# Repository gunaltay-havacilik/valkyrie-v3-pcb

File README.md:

# Valkyrie Flight Control Computer V3.1

Made using primarily KiCad version 9.0<br/>
Some 3D files might not be assigned correctly. You have been warned.<br/>
Uses JLCPCB JLC04161H-7628 stackup, 4 layer.

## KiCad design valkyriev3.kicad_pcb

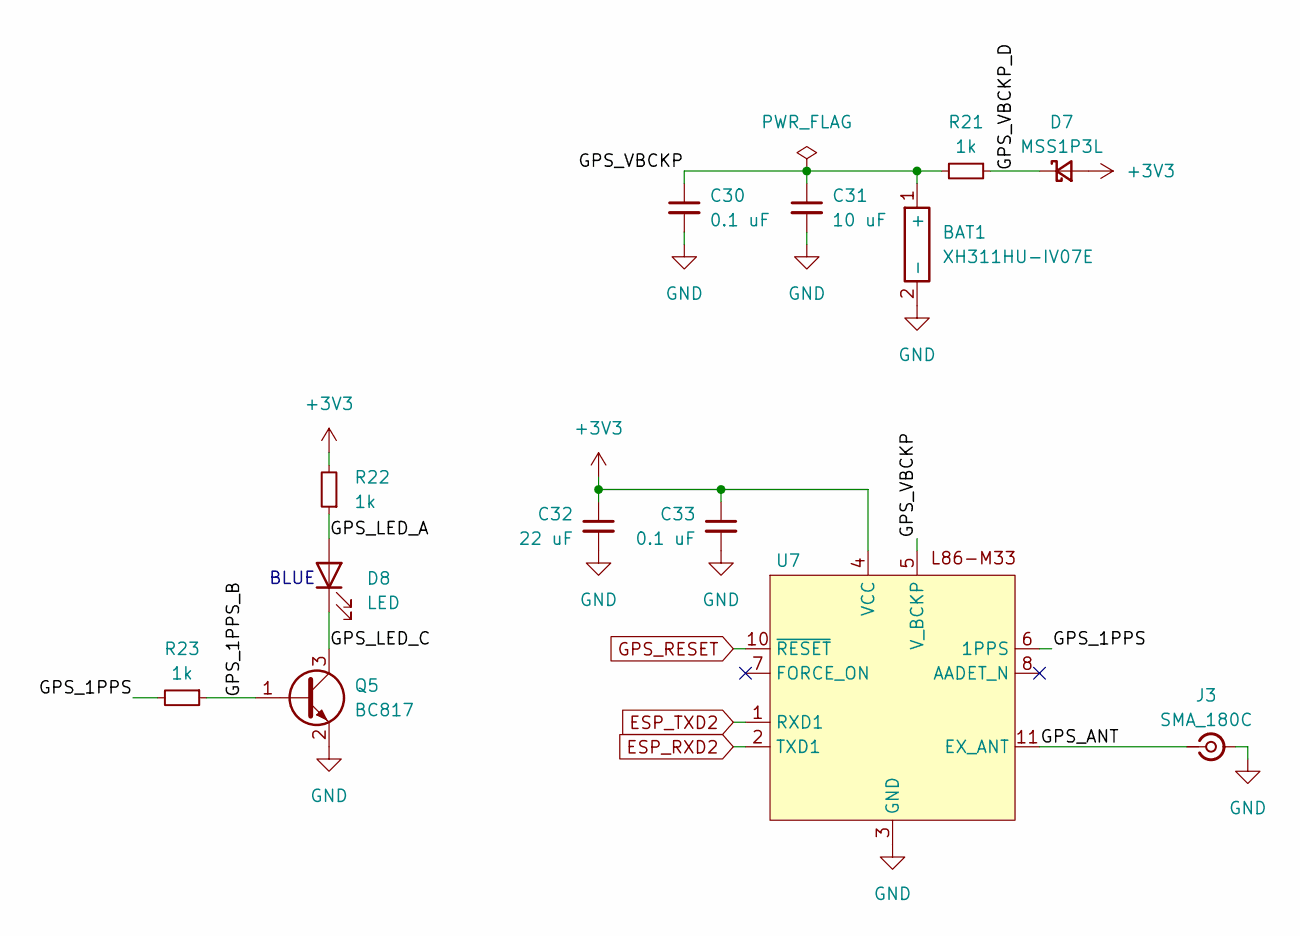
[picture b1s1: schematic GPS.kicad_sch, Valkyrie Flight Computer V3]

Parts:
BAT1: XH311HU-IV07E
C30, C33: 0.1 uF; C_0603_1608Metric
C31: 10 uF; C_0603_1608Metric
C32: 22 uF; C_0603_1608Metric
D7: MSS1P3L; D_MicroSMP_AK
D8: LED; LED_0603_1608Metric
J3: SMA_180C; SMA_Amphenol_132134-16_Vertical
Q5: BC817; SOT-23
R21, R22, R23: 1k; R_0603_1608Metric
U7: Quectel_L86-M33

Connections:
+3V3: C32.1, C33.1, D7.2 (A), R22.2, U7.4 (VCC); also elsewhere on the board
/GPS/GPS_1PPS: R23.2, U7.6 (1PPS)
/GPS/GPS_1PPS_B: Q5.1 (B), R23.1
/GPS/GPS_ANT: J3.1 (In), U7.11 (EX_ANT)
/GPS/GPS_LED_A: D8.2 (A), R22.1
/GPS/GPS_LED_C: D8.1 (K), Q5.3 (C)
/GPS/GPS_VBCKP: BAT1.1 (+), C30.1, C31.1, R21.2, U7.5 (V_BCKP)
/GPS/GPS_VBCKP_D: D7.1 (K), R21.1
ESP_RXD2: U7.2 (TXD1); also elsewhere on the board
ESP_TXD2: U7.1 (RXD1); also elsewhere on the board
GND: BAT1.2 (-), C30.2, C31.2, C32.2, C33.2, J3.2 (Ext), Q5.2 (E), U7.3 (GND), U7.12 (GND); also elsewhere on the board
GPS_RESET: U7.10 (~RESET); also elsewhere on the board

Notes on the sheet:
BLUE

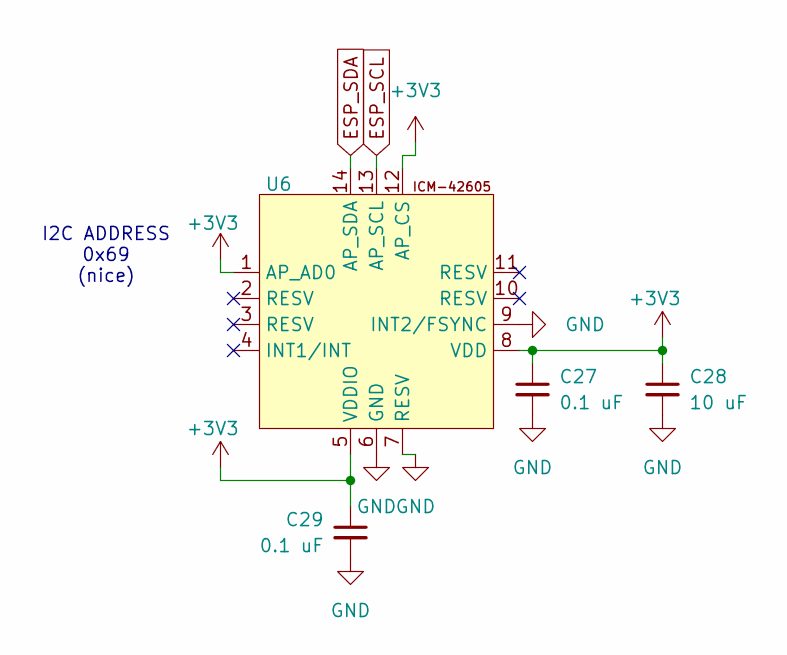
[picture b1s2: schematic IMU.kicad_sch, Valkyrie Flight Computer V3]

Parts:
C27, C29: 0.1 uF; C_0603_1608Metric
C28: 10 uF; C_0603_1608Metric
U6: LGA-14_3x2.5mm_P0.5mm_LayoutBorder3x4y

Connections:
+3V3: C27.1, C28.1, C29.1, U6.1 (AP_AD0), U6.5 (VDDIO), U6.8 (VDD), U6.12 (AP_CS); also elsewhere on the board
ESP_SCL: U6.13 (AP_SCL); also elsewhere on the board
ESP_SDA: U6.14 (AP_SDA); also elsewhere on the board
GND: C27.2, C28.2, C29.2, U6.6 (GND), U6.7 (RESV), U6.9 (INT2/FSYNC); also elsewhere on the board

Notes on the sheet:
I2C ADDRESS 0x69 (nice)

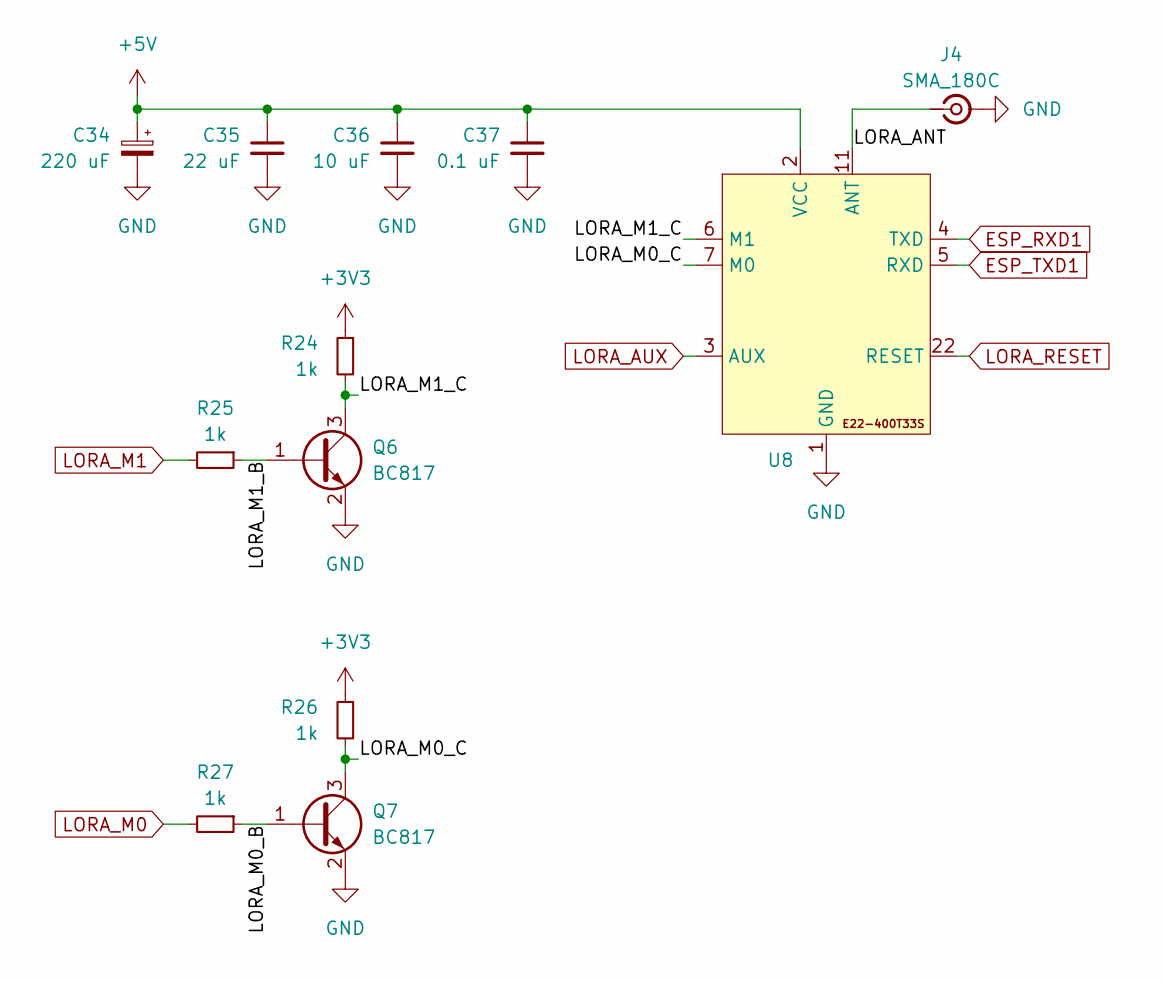
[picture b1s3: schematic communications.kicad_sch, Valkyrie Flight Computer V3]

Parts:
C34: 220 uF; CP_Elec_6.3x7.7
C35: 22 uF; C_0603_1608Metric
C36: 10 uF; C_0603_1608Metric
C37: 0.1 uF; C_0603_1608Metric
J4: SMA_180C; SMA_Amphenol_132134-16_Vertical
Q6, Q7: BC817; SOT-23
R24, R25, R26, R27: 1k; R_0603_1608Metric
U8: E22-400T33S

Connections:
+3V3: R24.1, R26.1; also elsewhere on the board
+5V: C34.1, C35.1, C36.1, C37.1, U8.2 (VCC); also elsewhere on the board
/Communications/LORA_ANT: J4.1 (In), U8.11 (ANT)
/Communications/LORA_M0_B: Q7.1 (B), R27.1
/Communications/LORA_M0_C: Q7.3 (C), R26.2, U8.7 (M0)
/Communications/LORA_M1_B: Q6.1 (B), R25.1
/Communications/LORA_M1_C: Q6.3 (C), R24.2, U8.6 (M1)
ESP_RXD1: U8.4 (TXD); also elsewhere on the board
ESP_TXD1: U8.5 (RXD); also elsewhere on the board
GND: C34.2, C35.2, C36.2, C37.2, J4.2 (Ext), Q6.2 (E), Q7.2 (E), U8.1 (GND), U8.12 (GND), U8.13 (GND), U8.14 (GND), U8.23 (GND); also elsewhere on the board
LORA_AUX: U8.3 (AUX); also elsewhere on the board
LORA_M0: R27.2; also elsewhere on the board
LORA_M1: R25.2; also elsewhere on the board
LORA_RESET: U8.22 (RESET); also elsewhere on the board

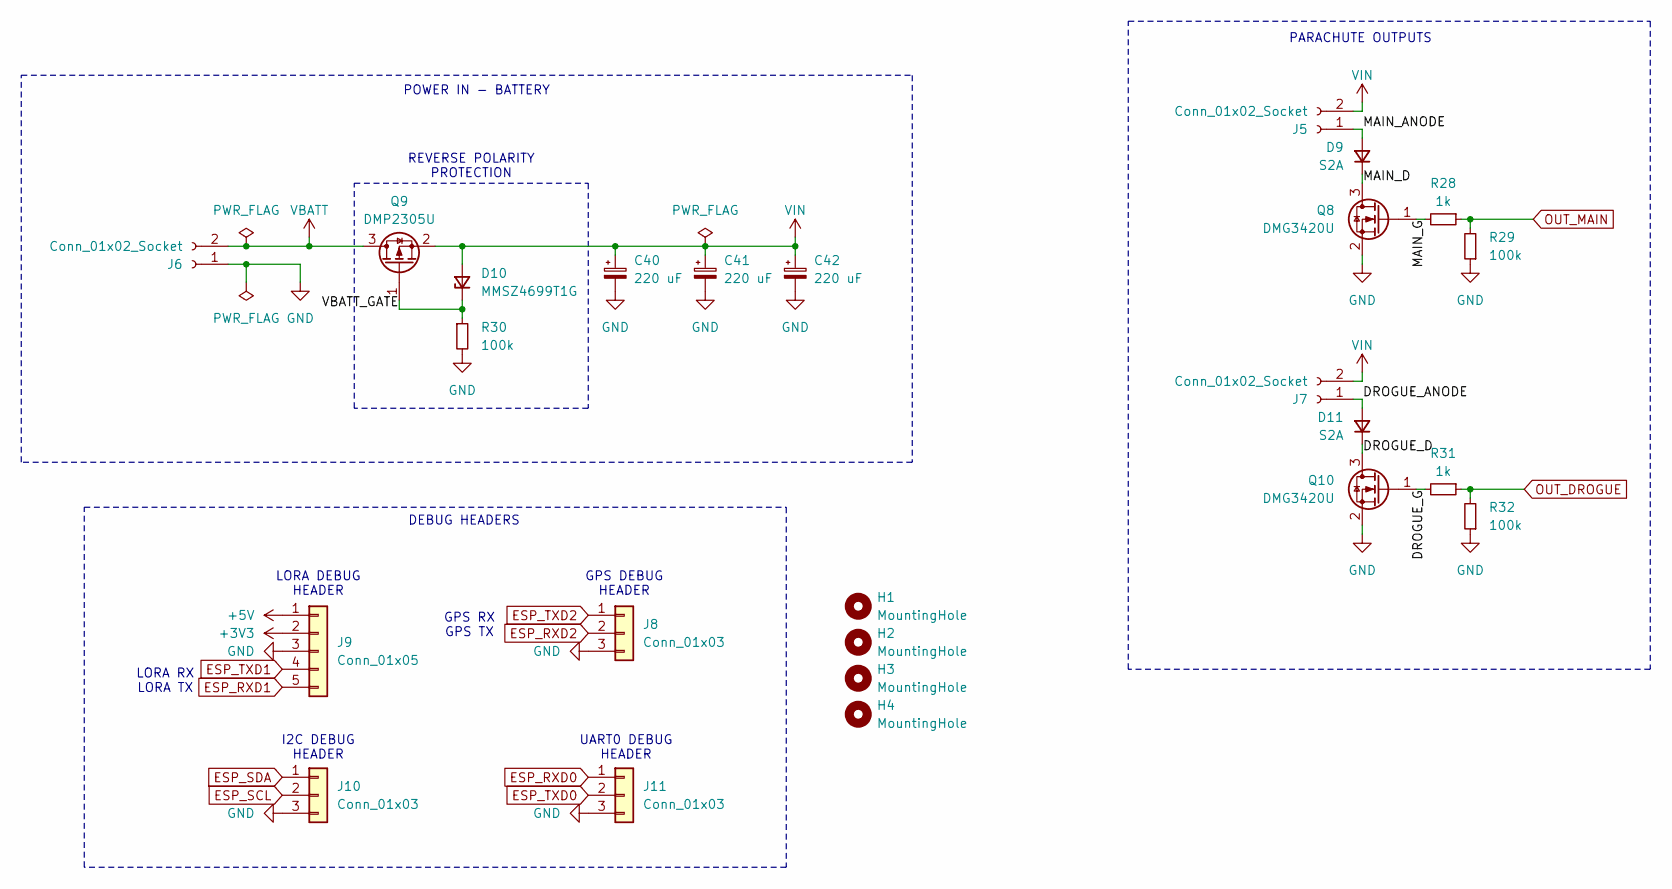
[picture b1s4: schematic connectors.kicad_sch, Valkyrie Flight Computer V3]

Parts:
C40, C41, C42: 220 uF; CP_Elec_6.3x7.7
D9, D11: S2A; D_SMB
D10: MMSZ4699T1G; D_SOD-123
H1, H2, H3, H4: MountingHole; MountingHole_2.2mm_M2
J5, J6, J7: Conn_01x02_Socket; AMASS_XT30PW-M_1x02_P2.50mm_Horizontal
J8, J10, J11: Conn_01x03; PinHeader_1x03_P2.54mm_Vertical
J9: Conn_01x05; PinHeader_1x05_P2.54mm_Vertical
Q8, Q10: DMG3420U; SOT-23
Q9: DMP2305U; SOT-23
R28, R31: 1k; R_0603_1608Metric
R29, R30, R32: 100k; R_0603_1608Metric

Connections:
+3V3: J9.2; also elsewhere on the board
+5V: J9.1; also elsewhere on the board
/Connectors/DROGUE_ANODE: D11.2 (A), J7.1
/Connectors/DROGUE_D: D11.1 (K), Q10.3 (D)
/Connectors/DROGUE_G: Q10.1 (G), R31.2
/Connectors/MAIN_ANODE: D9.2 (A), J5.1
/Connectors/MAIN_D: D9.1 (K), Q8.3 (D)
/Connectors/MAIN_G: Q8.1 (G), R28.2
/Connectors/VBATT_GATE: D10.1 (K), Q9.1 (G), R30.1
ESP_RXD0: J11.1; also elsewhere on the board
ESP_RXD1: J9.5; also elsewhere on the board
ESP_RXD2: J8.2; also elsewhere on the board
ESP_SCL: J10.2; also elsewhere on the board
ESP_SDA: J10.1; also elsewhere on the board
ESP_TXD0: J11.2; also elsewhere on the board
ESP_TXD1: J9.4; also elsewhere on the board
ESP_TXD2: J8.1; also elsewhere on the board
GND: C40.2, C41.2, C42.2, J6.1, J8.3, J9.3, J10.3, J11.3, Q8.2 (S), Q10.2 (S), R29.1, R30.2, R32.1; also elsewhere on the board
OUT_DROGUE: R31.1, R32.2; also elsewhere on the board
OUT_MAIN: R28.1, R29.2; also elsewhere on the board
VBATT: J6.2, Q9.3 (D)
VIN: C40.1, C41.1, C42.1, D10.2 (A), J5.2, J7.2, Q9.2 (S); also elsewhere on the board

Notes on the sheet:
LORA DEBUG HEADER
POWER IN - BATTERY
LORA RX LORA TX
PARACHUTE OUTPUTS
I2C DEBUG HEADER
UART0 DEBUG HEADER
DEBUG HEADERS
REVERSE POLARITY PROTECTION
GPS DEBUG HEADER
GPS RX GPS TX

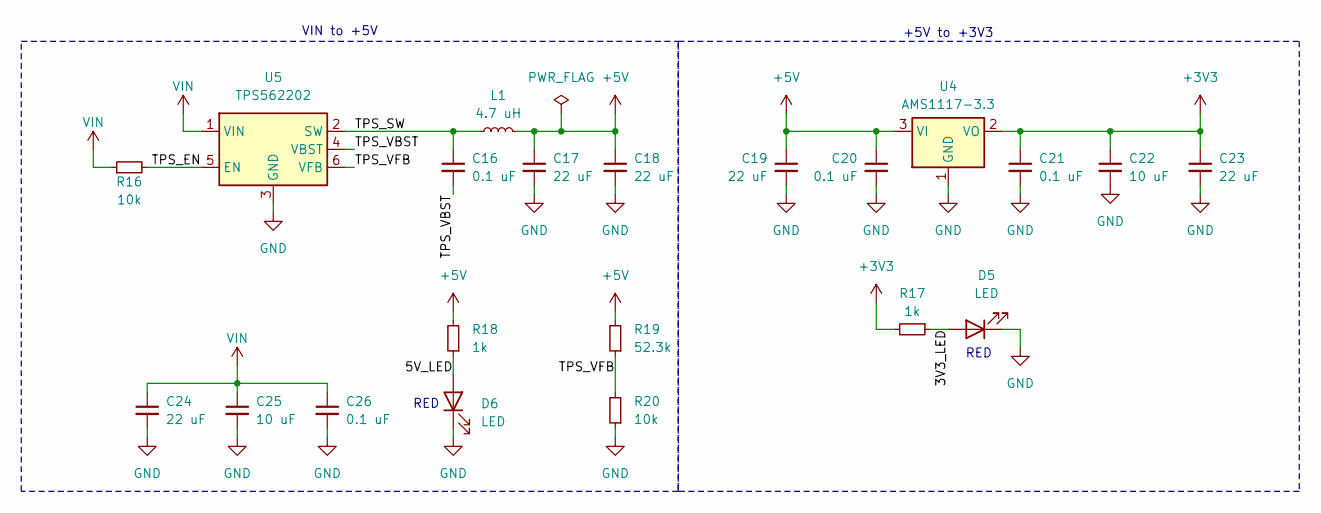
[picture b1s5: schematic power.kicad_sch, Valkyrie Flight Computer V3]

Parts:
C16, C20, C21: 0.1 uF; C_0603_1608Metric
C17, C18, C19, C23: 22 uF; C_0603_1608Metric
C22: 10 uF; C_0603_1608Metric
C24: 22 uF; C_0805_2012Metric
C25: 10 uF; C_0805_2012Metric
C26: 0.1 uF; C_0805_2012Metric
D5, D6: LED; LED_0603_1608Metric
L1: 4.7 uH; HPC 5020NF
R16, R20: 10k; R_0603_1608Metric
R17, R18: 1k; R_0603_1608Metric
R19: 52.3k; R_0603_1608Metric
U4: AMS1117-3.3; SOT-223-3_TabPin2
U5: TPS562202; SOT-563

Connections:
+3V3: C21.1, C22.1, C23.1, R17.2, U4.2 (VO); also elsewhere on the board
+5V: C17.1, C18.1, C19.1, C20.1, L1.2, R18.2, R19.2, U4.3 (VI); also elsewhere on the board
/Power/3V3_LED: D5.2 (A), R17.1
/Power/5V_LED: D6.2 (A), R18.1
/Power/TPS_EN: R16.2, U5.5 (EN)
/Power/TPS_SW: C16.1, L1.1, U5.2 (SW)
/Power/TPS_VBST: C16.2, U5.4 (VBST)
/Power/TPS_VFB: R19.1, R20.2, U5.6 (VFB)
GND: C17.2, C18.2, C19.2, C20.2, C21.2, C22.2, C23.2, C24.2, C25.2, C26.2, D5.1 (K), D6.1 (K), R20.1, U4.1 (GND), U5.3 (GND); also elsewhere on the board
VIN: C24.1, C25.1, C26.1, R16.1, U5.1 (VIN); also elsewhere on the board

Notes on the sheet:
RED
VIN to +5V
+5V to +3V3

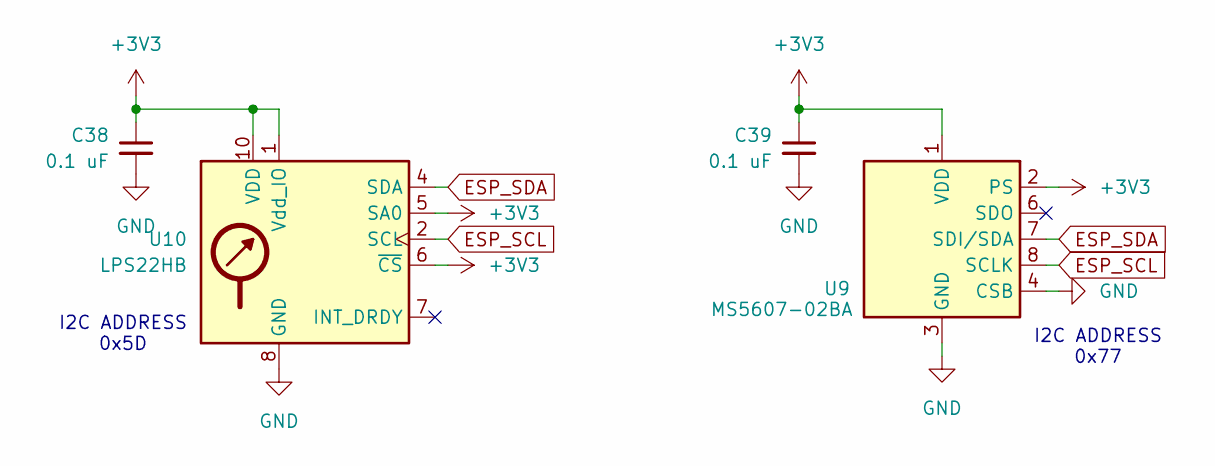
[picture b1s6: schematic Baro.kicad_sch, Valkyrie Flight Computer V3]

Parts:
C38, C39: 0.1 uF; C_0603_1608Metric
U9: MS5607-02BA; LGA-8_3x5mm_P1.25mm
U10: LPS22HB; ST_HLGA-10_2x2mm_P0.5mm_LayoutBorder3x2y

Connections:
+3V3: C38.1, C39.1, U9.1 (VDD), U9.2 (PS), U10.1 (Vdd_IO), U10.5 (SA0), U10.6 (~CS), U10.10 (VDD); also elsewhere on the board
ESP_SCL: U9.8 (SCLK), U10.2 (SCL); also elsewhere on the board
ESP_SDA: U9.7 (SDI/SDA), U10.4 (SDA); also elsewhere on the board
GND: C38.2, C39.2, U9.3 (GND), U9.4 (CSB), U9.5 (CSB), U10.3 (GND), U10.8 (GND), U10.9 (GND); also elsewhere on the board

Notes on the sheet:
I2C ADDRESS 0x5D
I2C ADDRESS 0x77

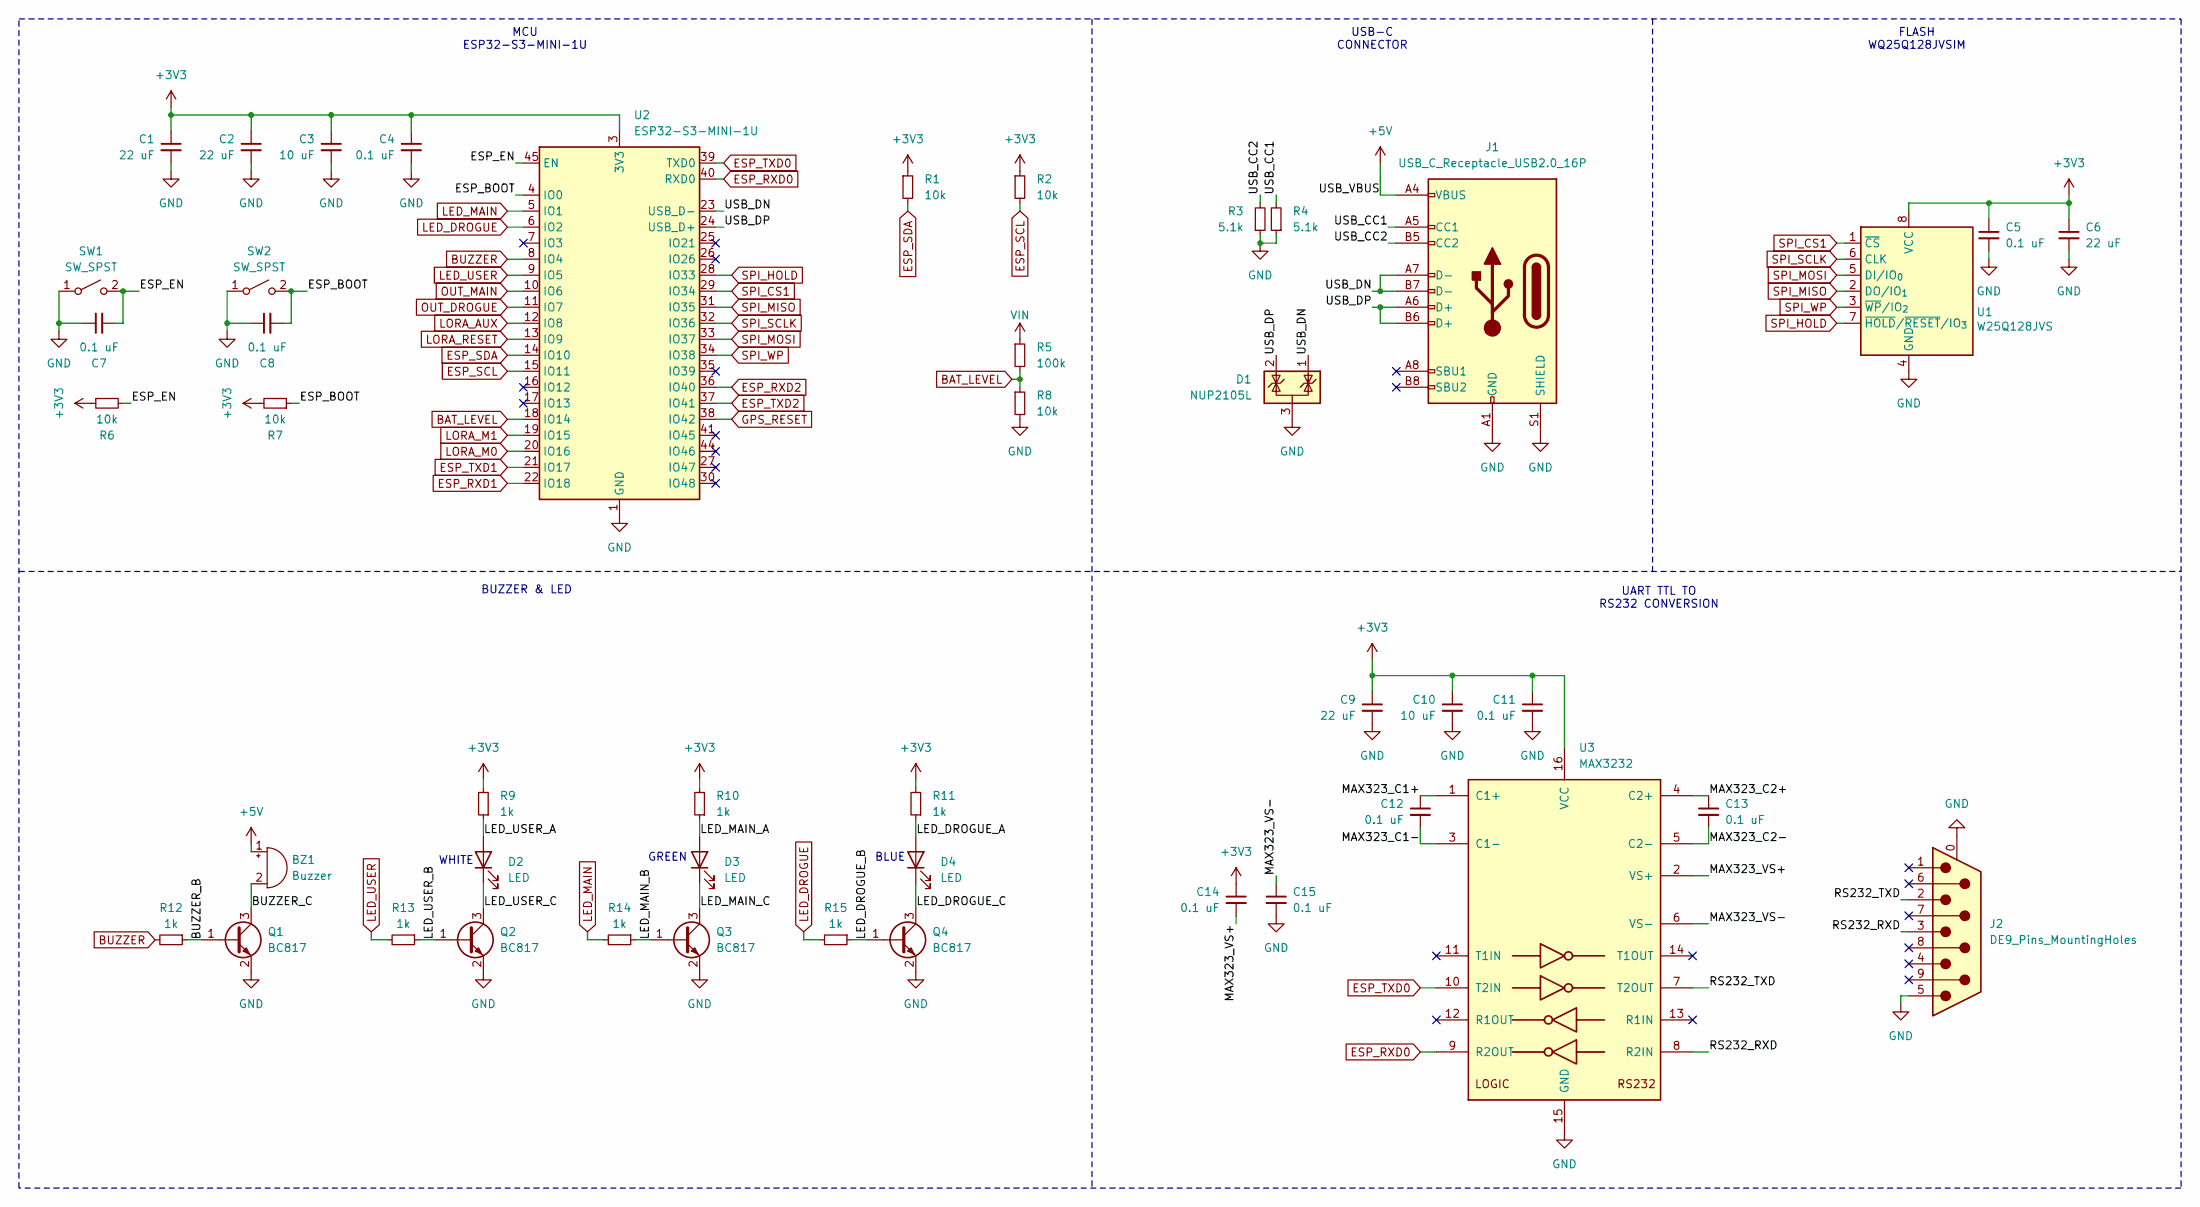
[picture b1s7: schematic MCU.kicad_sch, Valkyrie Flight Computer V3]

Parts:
BZ1: Buzzer; Buzzer_12x9.5RM7.6
C1, C2, C6, C9: 22 uF; C_0603_1608Metric
C3, C10: 10 uF; C_0603_1608Metric
C4, C5, C7, C8, C11, C12, C13, C14, C15: 0.1 uF; C_0603_1608Metric
D1: NUP2105L; SOT-23
D2, D3, D4: LED; LED_0603_1608Metric
J1: USB_C_Receptacle_USB2.0_16P; USB_C_Receptacle_GCT_USB4105-xx-A_16P_TopMnt_Horizontal
J2: DE9_Pins_MountingHoles; DSUB-9_Pins_Horizontal_P2.77x2.84mm_EdgePinOffset7.70mm_Hou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
Q1, Q2, Q3, Q4: BC817; SOT-23
R1, R2, R6, R7, R8: 10k; R_0603_1608Metric
R3, R4: 5.1k; R_0603_1608Metric
R5: 100k; R_0603_1608Metric
R9, R10, R11, R12, R13, R14, R15: 1k; R_0603_1608Metric
SW1, SW2: SW_SPST; SW_Tactile_SPST_NO_Straight_CK_PTS636Sx25SMTRLFS
U1: W25Q128JVS; SOIC-8_5.3x5.3mm_P1.27mm
U2: ESP32-S3-MINI-1U; ESP32-S2-MINI-1U
U3: MAX3232; TSSOP-16_4.4x5mm_P0.65mm

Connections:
+3V3: C1.1, C2.1, C3.1, C4.1, C5.1, C6.1, C9.1, C10.1, C11.1, C14.1, R1.1, R2.1, R6.1, R7.2, R9.2, R10.2, R11.2, U1.8 (VCC), U2.3 (3V3), U3.16 (VCC); also elsewhere on the board
+5V: BZ1.1 (+), J1.A4 (VBUS), J1.A9 (VBUS), J1.B4 (VBUS), J1.B9 (VBUS); also elsewhere on the board
/MCU/BUZZER_B: Q1.1 (B), R12.1
/MCU/BUZZER_C: BZ1.2 (-), Q1.3 (C)
/MCU/ESP_BOOT: C8.2, R7.1, SW2.2 (B), U2.4 (IO0)
/MCU/ESP_EN: C7.2, R6.2, SW1.2 (B), U2.45 (EN)
/MCU/LED_DROGUE_A: D4.2 (A), R11.1
/MCU/LED_DROGUE_B: Q4.1 (B), R15.1
/MCU/LED_DROGUE_C: D4.1 (K), Q4.3 (C)
/MCU/LED_MAIN_A: D3.2 (A), R10.1
/MCU/LED_MAIN_B: Q3.1 (B), R14.1
/MCU/LED_MAIN_C: D3.1 (K), Q3.3 (C)
/MCU/LED_USER_A: D2.2 (A), R9.1
/MCU/LED_USER_B: Q2.1 (B), R13.1
/MCU/LED_USER_C: D2.1 (K), Q2.3 (C)
/MCU/MAX323_C1+: C12.1, U3.1 (C1+)
/MCU/MAX323_C1-: C12.2, U3.3 (C1-)
/MCU/MAX323_C2+: C13.1, U3.4 (C2+)
/MCU/MAX323_C2-: C13.2, U3.5 (C2-)
/MCU/MAX323_VS+: C14.2, U3.2 (VS+)
/MCU/MAX323_VS-: C15.1, U3.6 (VS-)
/MCU/RS232_RXD: J2.3, U3.8 (R2IN)
/MCU/RS232_TXD: J2.2, U3.7 (T2OUT)
/MCU/USB_CC1: J1.A5 (CC1), R4.2
/MCU/USB_CC2: J1.B5 (CC2), R3.2
/MCU/USB_DN: D1.1 (K), J1.A7 (D-), J1.B7 (D-), U2.23 (USB_D-)
/MCU/USB_DP: D1.2 (K), J1.A6 (D+), J1.B6 (D+), U2.24 (USB_D+)
BAT_LEVEL: R5.2, R8.1, U2.18 (IO14)
BUZZER: R12.2, U2.8 (IO4)
ESP_RXD0: U2.40 (RXD0), U3.9 (R2OUT); also elsewhere on the board
ESP_RXD1: U2.22 (IO18); also elsewhere on the board
ESP_RXD2: U2.36 (IO40); also elsewhere on the board
ESP_SCL: R2.2, U2.15 (IO11); also elsewhere on the board
ESP_SDA: R1.2, U2.14 (IO10); also elsewhere on the board
ESP_TXD0: U2.39 (TXD0), U3.10 (T2IN); also elsewhere on the board
ESP_TXD1: U2.21 (IO17); also elsewhere on the board
ESP_TXD2: U2.37 (IO41); also elsewhere on the board
GND: C1.2, C2.2, C3.2, C4.2, C5.2, C6.2, C7.1, C8.1, C9.2, C10.2, C11.2, C15.2, D1.3 (A), J1.A1 (GND), J1.A12 (GND), J1.B1 (GND), J1.B12 (GND), J1.S1 (SHIELD), J2.0 (PAD), J2.5, Q1.2 (E), Q2.2 (E), Q3.2 (E), Q4.2 (E), R3.1, R4.1, R8.2, SW1.1 (A), SW2.1 (A), U1.4 (GND), U2.1 (GND), U2.2 (GND), U2.42 (GND), U2.43 (GND), U2.46 (GND), U2.47 (GND), U2.48 (GND), U2.49 (GND), U2.50 (GND), U2.51 (GND), U2.52 (GND), U2.53 (GND), U2.54 (GND), U2.55 (GND), U2.56 (GND), U2.57 (GND), U2.58 (GND), U2.59 (GND), U2.60 (GND), U2.61 (GND), U2.62 (GND), U2.63 (GND), U2.64 (GND), U2.65 (GND), U3.15 (GND); also elsewhere on the board
GPS_RESET: U2.38 (IO42); also elsewhere on the board
LED_DROGUE: R15.2, U2.6 (IO2)
LED_MAIN: R14.2, U2.5 (IO1)
LED_USER: R13.2, U2.9 (IO5)
LORA_AUX: U2.12 (IO8); also elsewhere on the board
LORA_M0: U2.20 (IO16); also elsewhere on the board
LORA_M1: U2.19 (IO15); also elsewhere on the board
LORA_RESET: U2.13 (IO9); also elsewhere on the board
OUT_DROGUE: U2.11 (IO7); also elsewhere on the board
OUT_MAIN: U2.10 (IO6); also elsewhere on the board
SPI_CS1: U1.1 (~CS), U2.29 (IO34)
SPI_HOLD: U1.7 (~HOLD/~RESET/IO_{3}), U2.28 (IO33)
SPI_MISO: U1.2 (DO/IO_{1}), U2.31 (IO35)
SPI_MOSI: U1.5 (DI/IO_{0}), U2.33 (IO37)
SPI_SCLK: U1.6 (CLK), U2.32 (IO36)
SPI_WP: U1.3 (~WP/IO_{2}), U2.34 (IO38)
VIN: R5.1; also elsewhere on the board

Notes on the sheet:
USB-C CONNECTOR
UART TTL TO RS232 CONVERSION
GREEN
WHITE
BLUE
FLASH WQ25Q128JVSIM
MCU ESP32-S3-MINI-1U
BUZZER & LED

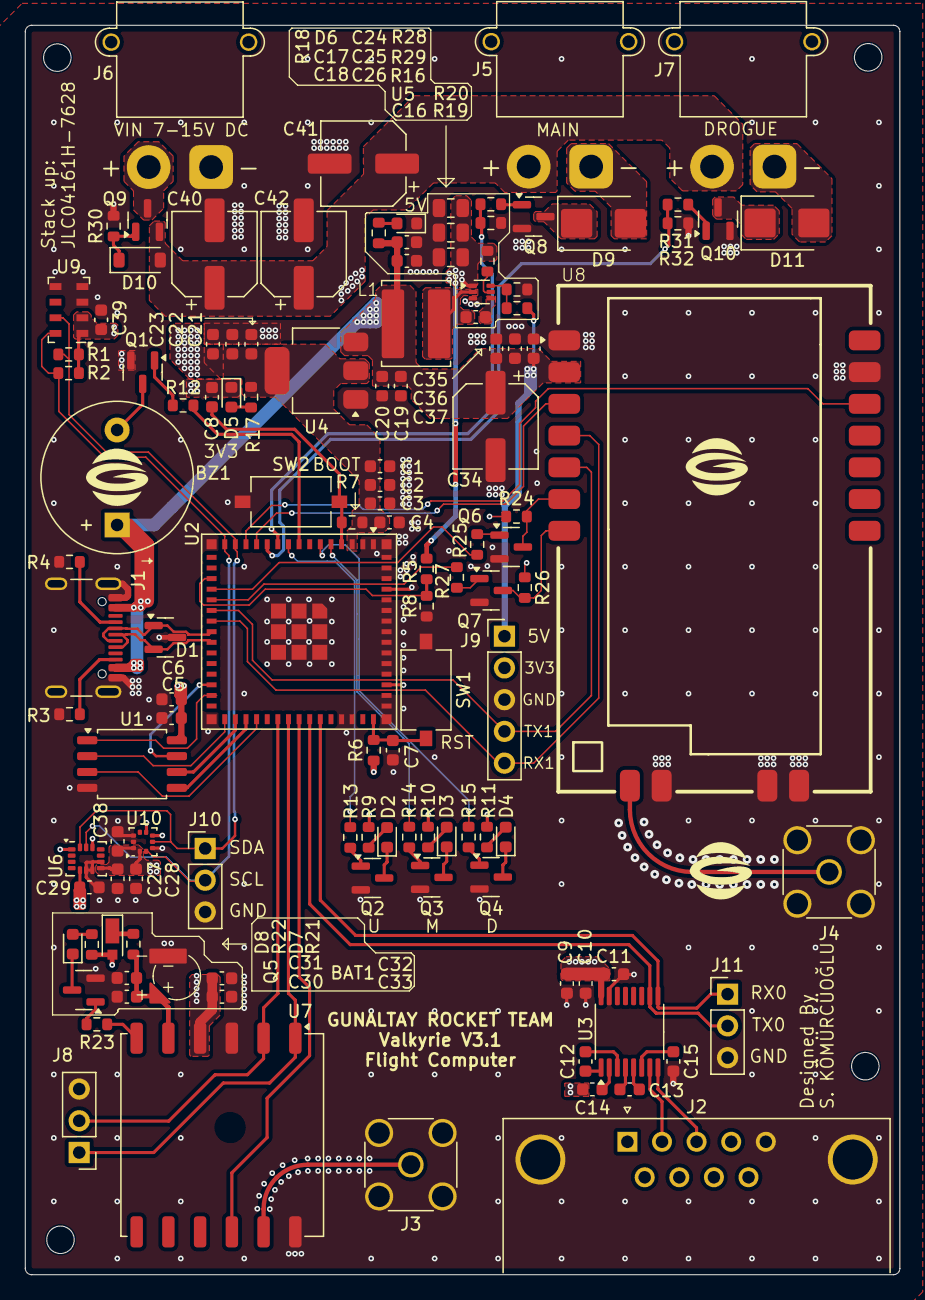
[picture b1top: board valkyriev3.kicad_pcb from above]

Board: 4 copper layers, 70.0 x 100.0 mm, 125 parts (0 on the bottom side), 81 nets.

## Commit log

2025-02-22 buzzer sch connections
2025-02-23 Wired barometers and GPS up, added misc LEDs, tidy-up
2025-02-24 preliminary schematic wired, all footprints assigned, all laid out in PCB editor.
2025-02-26 reassigned some footprints, preliminary PCB layout
2025-02-26 added missing output diodes, added 3d models, misc. re-laying
2025-02-26 3d model files
2025-02-28 revision of layout. added 3d model of the card
2025-04-03 updated some values and routed some preliminary roads
2025-04-04 completed routing. laid out reference designators, information and two anime girls
2025-04-05 Added BOOT and RST labels to their respective buttons
2025-04-05 connected IMU pins 7 and 9 to GND instead of NC
2025-04-05 connected missing grounds
2025-04-05 added my name as reviewer to pcb
2025-04-05 fixed unconnected grounds
2025-04-05 added esat's image
2025-04-05 added labels to headers and leds, configured severities of DRC checks
2025-04-05 generated JLC production files, configured .gitignore
2025-04-05 configure .gitignore
2025-04-05 remove backup files from git
2025-04-05 widened VIN track going to 5V SMPS
2025-04-08 added interactive BOM
2025-05-14 added sma 3d file
2025-05-19 added todo list
2025-06-22 did some clean-up, did some to-do tasks.
2025-07-26 improvements, re-did some tasks. updated step file.
2025-08-03 Added more graphics, removed some unnecessary features. moved GPU passive components upper. added switching components to LoRa.
2025-08-03 bumped version to v3.1
2026-03-25 Add README.md
2026-03-25 Add README.md (#1)
2026-03-26 fix line breaks in README
2026-03-26 fix line breaks in README (#2)
